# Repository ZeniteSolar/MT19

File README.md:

# MT19
Tachometer Module for CANBUS with ATmega328p

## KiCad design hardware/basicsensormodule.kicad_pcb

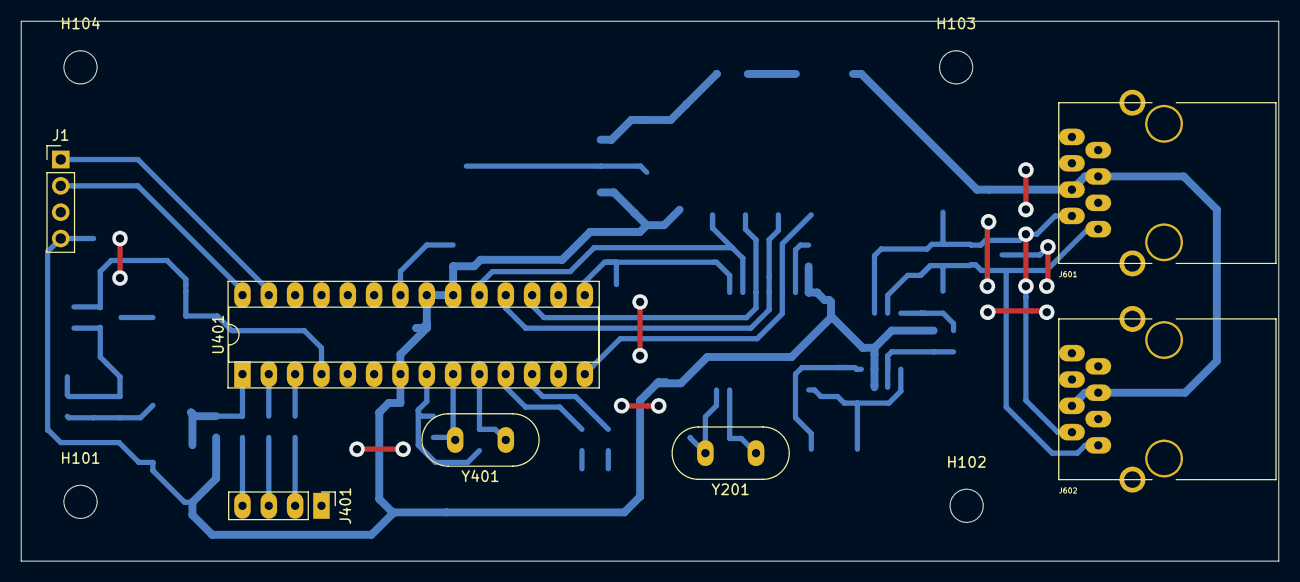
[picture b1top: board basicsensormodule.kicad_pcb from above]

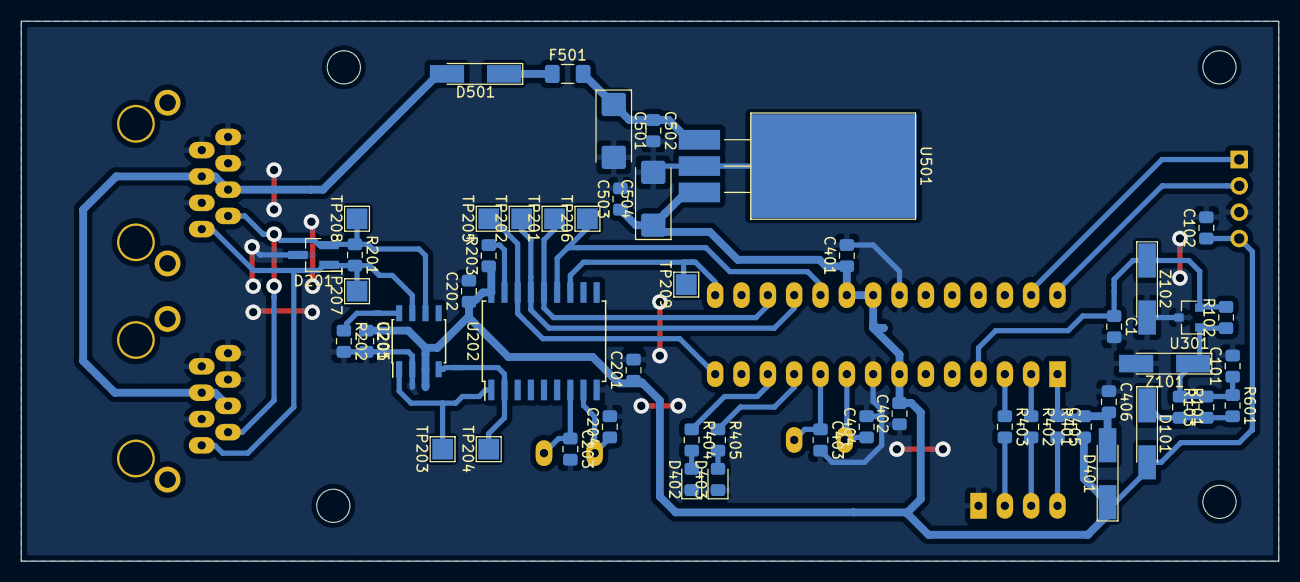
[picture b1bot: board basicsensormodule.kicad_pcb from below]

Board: 2 copper layers, 121.3 x 52.1 mm, 63 parts (52 on the bottom side), 35 nets.

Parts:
C1: 4.7n; C_0805_2012Metric_Pad1.15x1.40mm_HandSolder
C101: 100n; C_0805_2012Metric_Pad1.15x1.40mm_HandSolder
C102, C201, C202, C205, C401, C402, C405, C406, C502, C503: 100nF; C_0805_2012Metric_Pad1.15x1.40mm_HandSolder
C203, C204, C403, C404: 22pF; C_0805_2012Metric_Pad1.15x1.40mm_HandSolder
C501, C504: 1uF; CP_EIA-6032-20_AVX-F_Pad2.25x2.35mm_HandSolder
D101, D401, D501: LL4148; D_MiniMELF_Handsoldering
D201: pesd1can; SOT-23_Handsoldering
D402, D403: LED_RED; LED_0805_2012Metric_Pad1.15x1.40mm_HandSolder
F501: 500mA; Fuse_1206_3216Metric_Pad1.42x1.75mm_HandSolder
H101, H102, H103, H104: MountingHole; MountingHole_3.2mm_M3
J1: Conn_01x04; PinHeader_1x04_P2.54mm_Vertical
J401: USART; PinHeader_1x04_P2.54mm_Vertical
J601, J602: RJ45; RJ45_YH59_01
R101, R103, R601: 330; R_0805_2012Metric_Pad1.15x1.40mm_HandSolder
R102, R203, R401: 10k; R_0805_2012Metric_Pad1.15x1.40mm_HandSolder
R201: 120; R_0805_2012Metric_Pad1.15x1.40mm_HandSolder
R202: 4k7; R_0805_2012Metric_Pad1.15x1.40mm_HandSolder
R402, R403, R404, R405: 1k; R_0805_2012Metric_Pad1.15x1.40mm_HandSolder
TP201: SI; TestPoint_Pad_2.0x2.0mm
TP202: SO; TestPoint_Pad_2.0x2.0mm
TP203: TXCAN; TestPoint_Pad_2.0x2.0mm
TP204: RXCAN; TestPoint_Pad_2.0x2.0mm
TP205: SC; TestPoint_Pad_2.0x2.0mm
TP206: SCK; TestPoint_Pad_2.0x2.0mm
TP207: CAN_H; TestPoint_Pad_2.0x2.0mm
TP208: CAN_L; TestPoint_Pad_2.0x2.0mm
TP209: INT; TestPoint_Pad_2.0x2.0mm
U201: MCP2551-I/SN; SOIC-8_3.9x4.9mm_P1.27mm
U202: MCP2515-xSO; SOIC-18W_7.5x11.6mm_P1.27mm
U301: A1101ELHL; SOT-23
U401: ATMEGA328P-PU; DIP-28_W7.62mm_Socket
U501: LM7805; TO-220-3_Horizontal_TabDown_SMD
Y201, Y401: 16MHz; Crystal_HC49-U_Vertical
Z101, Z102: 4.7V; D_MiniMELF_Handsoldering

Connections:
+5V: C102.1, C201.1, C202.1, C205.1, C401.1, C402.2, C503.1, C504.1, D101.2, D401.1, J1.4, R203.1, R401.1, U201.3, U202.18, U401.7, U401.20, U401.21, U501.3
/CANBUS CONN/CAN_H: D201.1, J601.1, J602.1, R201.2, TP207.1, U201.7
/CANBUS CONN/CAN_L: D201.2, J601.2, J602.2, R201.1, TP208.1, U201.6
/CANBUS/CS: TP205.1, U202.16, U401.14
/CANBUS/INT: TP209.1, U202.12, U401.15
/CANBUS/RXCAN: TP204.1, U201.4, U202.2
/CANBUS/TXCAN: TP203.1, U201.1, U202.1
/MCU/LED1: R405.1, U401.11
/MCU/LED2: R404.1, U401.12
/MCU/RESET: C405.1, C406.2, D401.2, R401.2, U401.1
/MCU/SCL: J1.2, U401.28
/MCU/SDA: J1.1, U401.27
/MCU/USART_RX: R402.1, U401.2
/MCU/USART_TX: R403.1, U401.3
/MCU/VOUT: C1.1, R102.2, U301.2, U401.4, Z102.1
/MISO: TP202.1, U202.15, U401.18
/MOSI: TP201.1, U202.14, U401.17
/POWER SUPPLY/+18V_IN: D501.2, J601.4, J601.5, J602.4, J602.5
/POWER SUPPLY/+18V_OUT: C501.1, C502.1, F501.2, U501.1
/SCK: TP206.1, U202.13, U401.19
GND: C1.2, C101.2, C102.2, C201.2, C202.2, C203.2, C204.2, C205.2, C401.2, C402.1, C403.2, C404.2, C406.1, C501.2, C502.2, C503.2, C504.2, D201.3, D402.1, D403.1, J1.3, J401.1, J601.3, J601.6, J601.7, J601.8, J602.3, J602.6, J602.7, J602.8, R202.2, U201.2, U202.9, U301.3, U401.8, U401.22, U501.2, Z101.2, Z102.2
unnamed: C101.1, R101.1, R102.1, R103.2, R601.1, U301.1, Z101.1
unnamed: C203.1, U202.7, Y201.1
unnamed: C204.1, U202.8, Y201.2
unnamed: C403.1, U401.10, Y401.1
unnamed: C404.1, U401.9, Y401.2
unnamed: C405.2, J401.4
unnamed: D101.1, R101.2, R103.1, R601.2
unnamed: D402.2, R404.2
unnamed: D403.2, R405.2
unnamed: D501.1, F501.1
unnamed: J401.2, R403.2
unnamed: J401.3, R402.2
unnamed: R202.1, U201.8
unnamed: R203.2, U202.17

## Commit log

2019-05-07 Arquivos iniciados do repositório MVC19
2019-05-07 Descrição básica adicionada
2019-05-09 Layout MT19 criado para o Taquímetro do barco.
2019-05-09 Módulo MT19 do tacômetro do barco
2019-05-09 Atualização MT19
2019-05-10 Atualização pdf MT19
2019-05-24 layout finalizado
2019-08-08 limpei a biblioteca do display
2019-08-08 atualizei o hardware
2019-08-08 CAN_IDS19 adicionado
2019-08-08 firmware atualizado
2019-08-08 porta modificada, display removido
2019-08-09 firmware finalizado
2020-01-19 3D exported
2020-01-20 avr-can-lib updated
2020-01-20 makelibs updated
2020-01-20 updating MAB CAN messages
2020-01-20 updating MT CAN messages
2020-01-20 cleaned
2020-01-21 updating MAM and GENERIC CAN messages
2020-01-21 Compiling. Need to be tested
2020-02-14 .gitignore updated
2021-12-14 Count time between pulses instead of pulses in a period.
2021-12-15 Fix rpm calculation and timer prescaler
2021-12-15 Use extern modifier to fix duplicated variables being defined on newer GCC
2021-12-16 Use default system-wide avr-gcc toolchain
2021-12-17 Change CAN CS pin because the previous one was PCINT0(Timer trigger interruption)
2021-12-17 Fix 0rpm and more small fixes
2021-12-17 add serial output in up script
2024-07-13 First tested/working version using time difference
2024-07-13 Update schematics, add BOM
